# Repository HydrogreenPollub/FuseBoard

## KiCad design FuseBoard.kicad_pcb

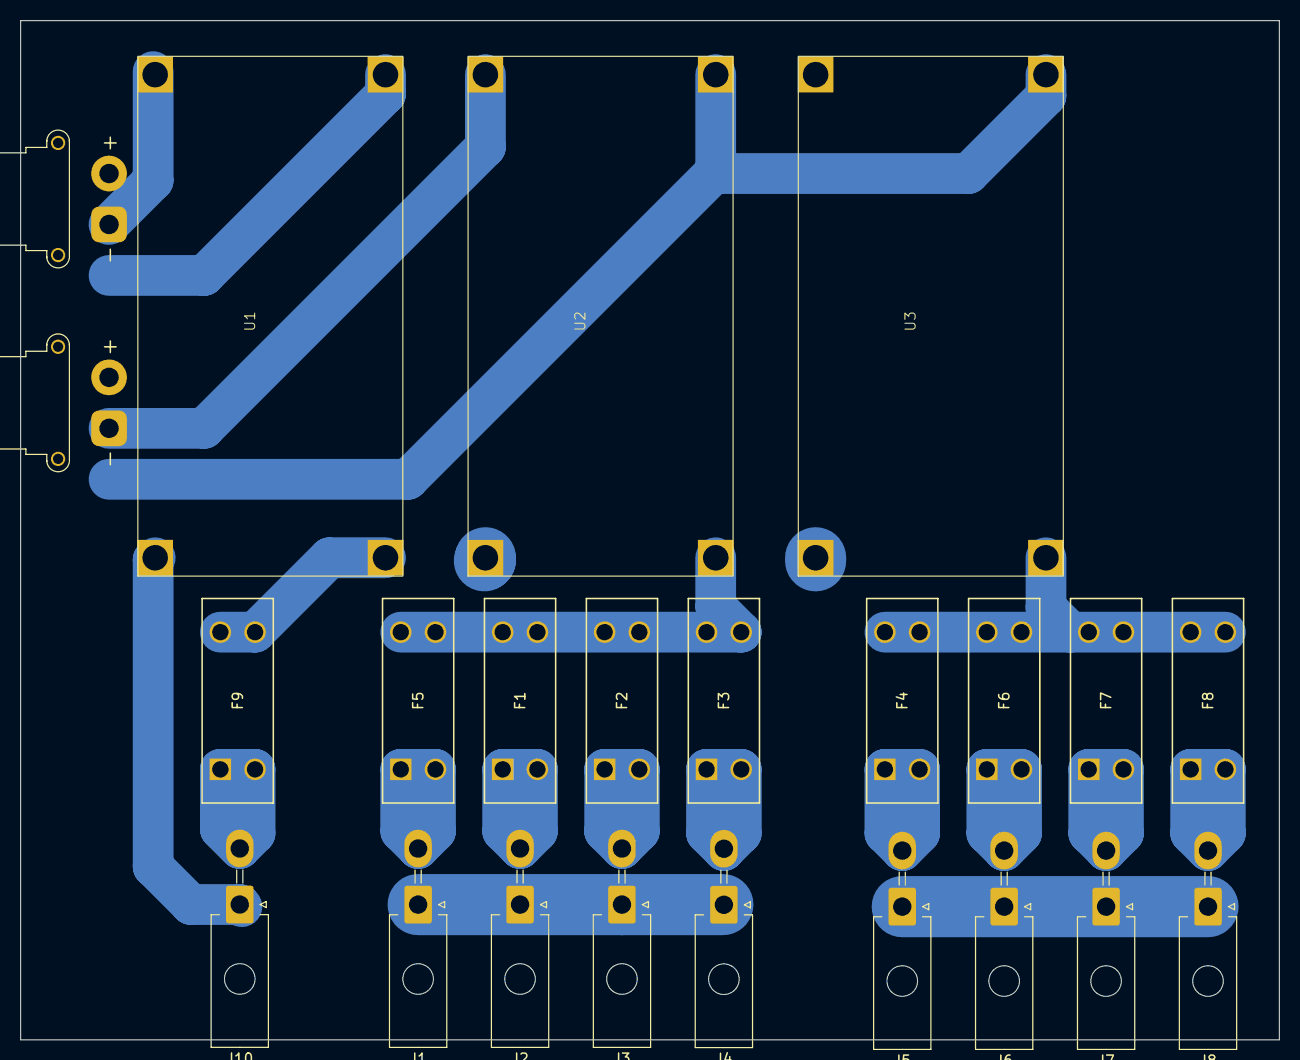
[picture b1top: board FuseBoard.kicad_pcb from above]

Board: 2 copper layers, 123.5 x 100.0 mm, 23 parts (0 on the bottom side), 15 nets.

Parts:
F1, F2, F3, F4, F5, F6, F7, F8, F9: 3557-10; 3557-10_KEY
J1, J2, J3, J4, J5, J6, J7, J8, J10: Conn_01x02_Socket; Molex_Mini-Fit_Jr_5569-02A2_2x01_P4.20mm_Horizontal
J9, J11: Conn_01x02_Socket; AMASS_XT30PW-F_1x02_P2.50mm_Horizontal
U1, U2, U3: XL4015E1_buck_converter_module

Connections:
+5V: F1.3, F1.4, F2.3, F2.4, F3.3, F3.4, F5.3, F5.4
+12V: F4.3, F4.4, F6.3, F6.4, F7.3, F7.4, F8.3, F8.4
GND1: J1.1, J2.1, J3.1, J4.1, U2.1
GND2: J5.1, J6.1, J7.1, J8.1, U3.1
unnamed: F5.1, F5.2, J1.2
unnamed: F1.1, F1.2, J2.2
unnamed: F2.1, F2.2, J3.2
unnamed: F3.1, F3.2, J4.2
unnamed: F4.1, F4.2, J5.2
unnamed: F6.1, F6.2, J6.2
unnamed: F7.1, F7.2, J7.2
unnamed: F8.1, F8.2, J8.2
unnamed: J10.1, J11.1
unnamed: F9.1, F9.2, J10.2
unnamed: F9.3, F9.4

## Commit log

2025-05-07 started work on board
2025-05-13 changes to pcb
2025-05-14 updated pcb
2025-05-23 separated GNDs
